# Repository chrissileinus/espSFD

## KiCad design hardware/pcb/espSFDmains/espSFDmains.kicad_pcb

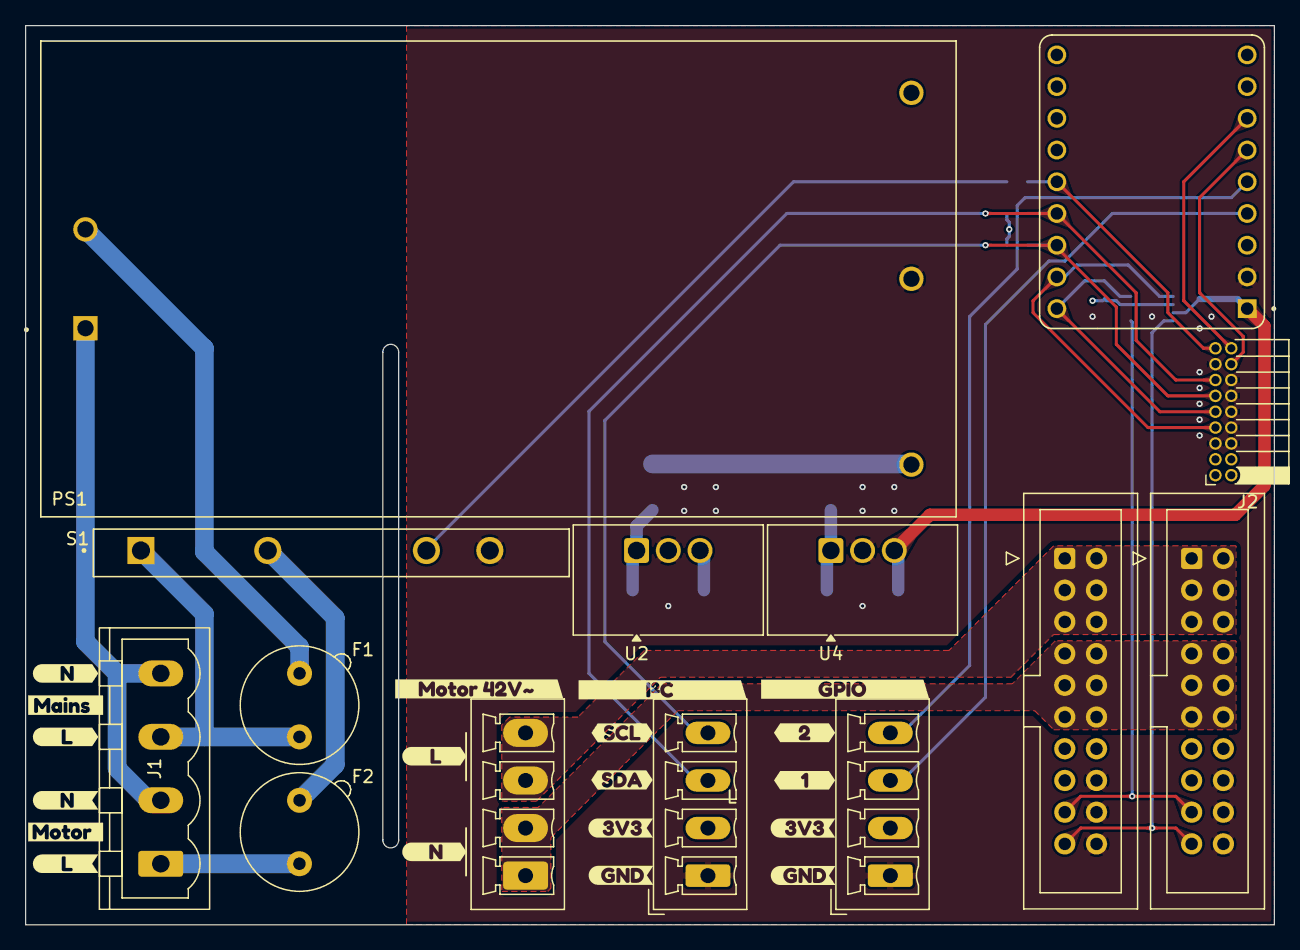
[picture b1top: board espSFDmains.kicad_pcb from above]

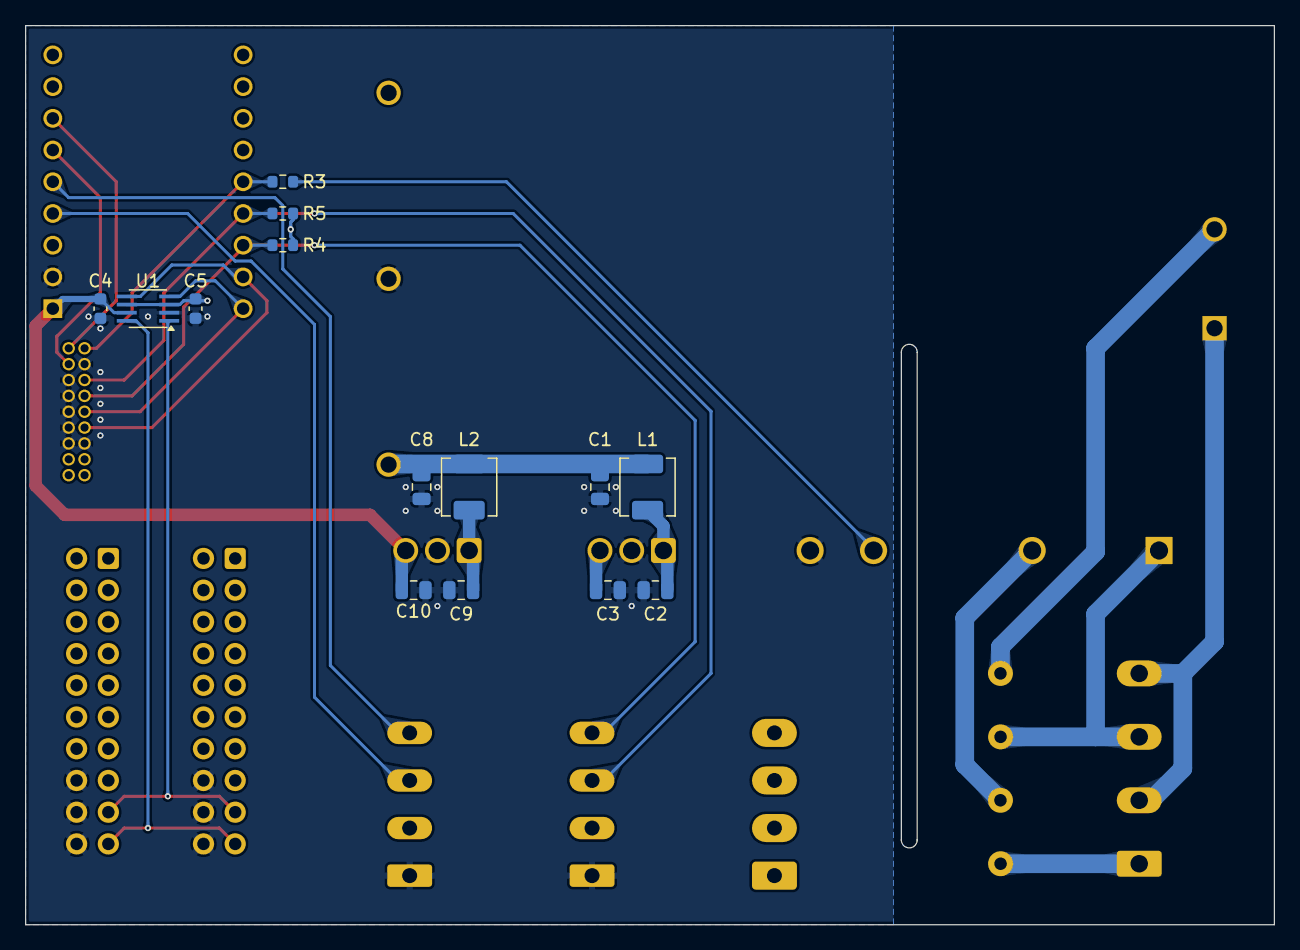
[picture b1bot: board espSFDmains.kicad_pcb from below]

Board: 4 copper layers, 100.0 x 72.0 mm, 47 parts (14 on the bottom side), 25 nets.

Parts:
C1, C2, C8, C9: 4.7µF 50V; C_0805_2012Metric
C3, C10: 10µF 25V; C_0805_2012Metric
C4, C5: 100nF/25V; C_0603_1608Metric
F1: 1A; Fuseholder_TR5_Littelfuse_No560_No460
F2: 6A; Fuseholder_TR5_Littelfuse_No560_No460
J1: Mains; PhoenixContact_MSTBVA_2,5_4-G-5,08_1x04_P5.08mm_Vertical
J2: Board Interconn; PinSocket_2x09_P1.27mm_Horizontal
J5: Motor; PhoenixContact_MCV_1,5_4-G-3.81_1x04_P3.81mm_Vertical
J8, J9: SFD Bus; IDC-Header_2x10_P2.54mm_Vertical
J10: D1 & D2; PhoenixContact_MCV_1,5_4-G-3.81_1x04_P3.81mm_Vertical
J11: D3 & D4; PhoenixContact_MCV_1,5_4-G-3.81_1x04_P3.81mm_Vertical
L1, L2: 4,7µH 3A; L_Sunlord_MWSA0402S
PS1: TPP_30-109-D
R3: 330R; R_0603_1608Metric
R4, R5: 4K7; R_0603_1608Metric
S1: CPC40055ST
U1: TXS0102DCT; SSOP-8_2.95x2.8mm_P0.65mm
U2: TSR3-2433N; Converter_DCDC_TRACO_TSR2-24xxN_TSR2-24xxxN_THT
U3: ESP32-S3-ZERO
U4: TSR3-2450N; Converter_DCDC_TRACO_TSR2-24xxN_TSR2-24xxxN_THT
kibuzzard-69B3E2B0: G***; kibuzzard-69B3E2B0
kibuzzard-69B3E2CA: G***; kibuzzard-69B3E2CA
kibuzzard-69B3E35C: G***; kibuzzard-69B3E35C
kibuzzard-69B3E36A: G***; kibuzzard-69B3E36A
kibuzzard-69B3E36E: G***; kibuzzard-69B3E36E
kibuzzard-69B3E37F: G***; kibuzzard-69B3E37F
kibuzzard-69B3E350: G***; kibuzzard-69B3E350
kibuzzard-69B3E357: G***; kibuzzard-69B3E357
kibuzzard-69B3E365: G***; kibuzzard-69B3E365
kibuzzard-69B3E379: G***; kibuzzard-69B3E379
kibuzzard-69B3E384: G***; kibuzzard-69B3E384
kibuzzard-69B3E389: G***; kibuzzard-69B3E389
kibuzzard-699C2DF3: G***; kibuzzard-699C2DF3
kibuzzard-699C2E08: G***; kibuzzard-699C2E08
kibuzzard-699C2E52: G***; kibuzzard-699C2E52
kibuzzard-699C2EF8: G***; kibuzzard-699C2EF8
kibuzzard-699C2F02: G***; kibuzzard-699C2F02
kibuzzard-6985EF5B: G***; kibuzzard-6985EF5B
kibuzzard-6985EF62: G***; kibuzzard-6985EF62

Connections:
230V Motor: F2.1, J1.1
+3.3V: C3.2, C5.2, J10.2, J11.2, R4.1, R5.1, U1.3 (VCCA), U1.6 (OE), U2.3 (Vout)
+5V: C4.2, C10.2, U1.7 (VCCB), U3.5V, U4.3 (Vout)
+9V: C1.2, C8.2, J2.1, J2.2, J2.3, J2.4, J8.13, J8.14, J8.15, J9.13, J9.14, J9.15, L1.1, L2.1, PS1.3 (+VOUT)
En Motor: J2.17, R3.1, U3.11 (GP11)
GND: C1.1, C2.1, C3.1, C4.1, C5.1, C8.1, C9.1, C10.1, J2.5, J2.6, J2.8, J2.10, J2.12, J2.14, J2.15, J8.16, J8.18, J8.20, J9.16, J9.18, J9.20, J10.1, J11.1, PS1.4 (-VOUT), S1.4 (-LED), U1.2 (GND), U2.2 (GND), U3.GND, U4.2 (GND)
GPIO1: J11.3, U3.1 (GP1)
GPIO2: J11.4, U3.2 (GP2)
GPIO3: J2.16, U3.3 (GP3)
GPIO4: J2.18, U3.4 (GP4)
LINE: F1.1, J1.3, S1.1 (AC_LOAD1)
Motor L: J5.1, J5.2, J8.7, J8.8, J8.9, J8.10, J8.11, J8.12, J9.7, J9.8, J9.9, J9.10, J9.11, J9.12
Motor N: J5.3, J5.4, J8.1, J8.2, J8.3, J8.4, J8.5, J8.6, J9.1, J9.2, J9.3, J9.4, J9.5, J9.6
NEUT: J1.2, J1.4, PS1.1 (NEUTRAL)
unnamed: F1.2, PS1.2 (LINE)
unnamed: R3.2, S1.3 (+LED)
unnamed: F2.2, S1.2 (AC_LOAD2)
unnamed: C2.2, L1.2, U2.1 (Vin)
unnamed: C9.2, L2.2, U4.1 (Vin)
RX: J8.19, J9.19, U1.8 (B1)
RX_: J2.7, U1.5 (A1), U3.RX
SCL: J2.11, J10.4, R4.2, U3.13 (GP13)
SDA: J2.13, J10.3, R5.2, U3.12 (GP12)
TX: J8.17, J9.17, U1.1 (B2)
TX_: J2.9, U1.4 (A2), U3.TX

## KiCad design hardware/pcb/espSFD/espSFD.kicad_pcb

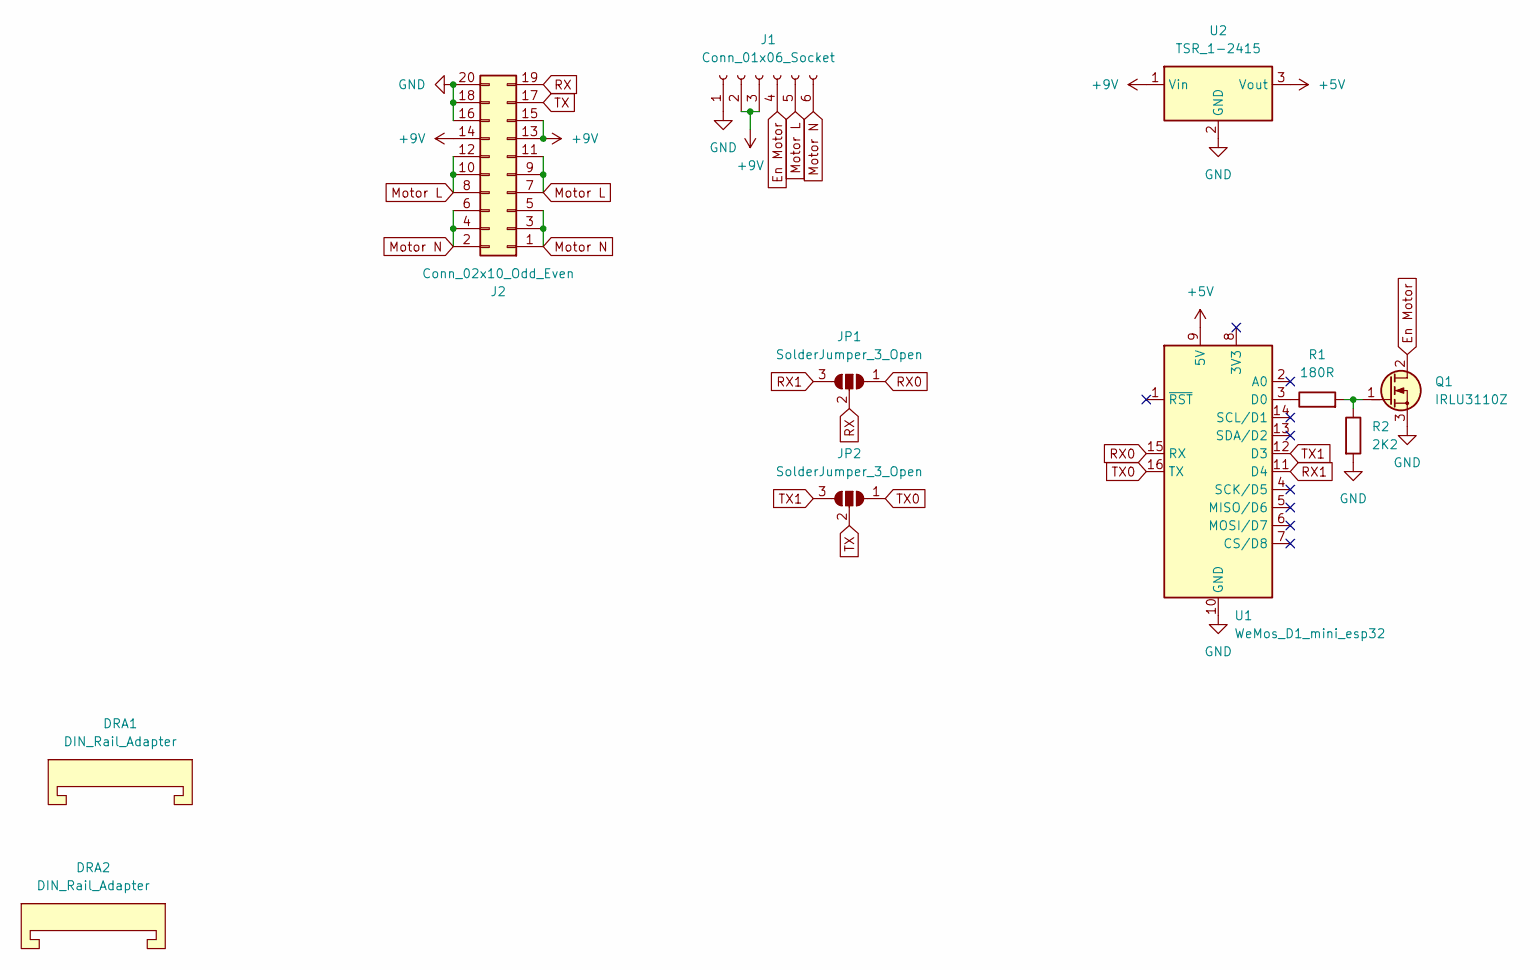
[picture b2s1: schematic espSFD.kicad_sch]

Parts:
DRA1, DRA2: DIN_Rail_Adapter; DINRailAdapter_3xM3_PhoenixContact_1201578
J1: Conn_01x06_Socket; PhoenixContact_MSTBA_2,5_6-G-5,08_1x06_P5.08mm_Horizontal
J2: Conn_02x10_Odd_Even; IDC-Header_2x10_P2.54mm_Vertical
JP1, JP2: SolderJumper_3_Open; SolderJumper-3_P1.3mm_Open_Pad1.0x1.5mm no silk
Q1: IRLU3110Z; TO-251-3_Vertical_GDS
R1: 180R; R_Axial_DIN0204_L3.6mm_D1.6mm_P7.62mm_Horizontal
R2: 2K2; R_Axial_DIN0204_L3.6mm_D1.6mm_P7.62mm_Horizontal
U1: WeMos_D1_mini_esp32; WEMOS_D1_mini_light
U2: TSR_1-2415; Converter_DCDC_TRACO_TSR-1_THT

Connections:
+5V: U1.9 (5V), U2.3 (Vout)
+9V: J1.2, J1.3, J2.13, J2.14, J2.15, U2.1 (Vin)
En Motor: J1.4, Q1.2 (D)
GND: J1.1, J2.16, J2.18, J2.20, Q1.3 (S), R2.2, U1.10 (GND), U2.2 (GND)
Motor L: J1.5, J2.7, J2.8, J2.9, J2.10, J2.11, J2.12
Motor N: J1.6, J2.1, J2.2, J2.3, J2.4, J2.5, J2.6
unnamed: Q1.1 (G), R1.2, R2.1
unnamed: R1.1, U1.3 (D0)
RX: J2.19, JP1.2 (C)
RX0: JP1.1 (A), U1.15 (RX)
RX1: JP1.3 (B), U1.11 (D4)
TX: J2.17, JP2.2 (C)
TX0: JP2.1 (A), U1.16 (TX)
TX1: JP2.3 (B), U1.12 (D3)

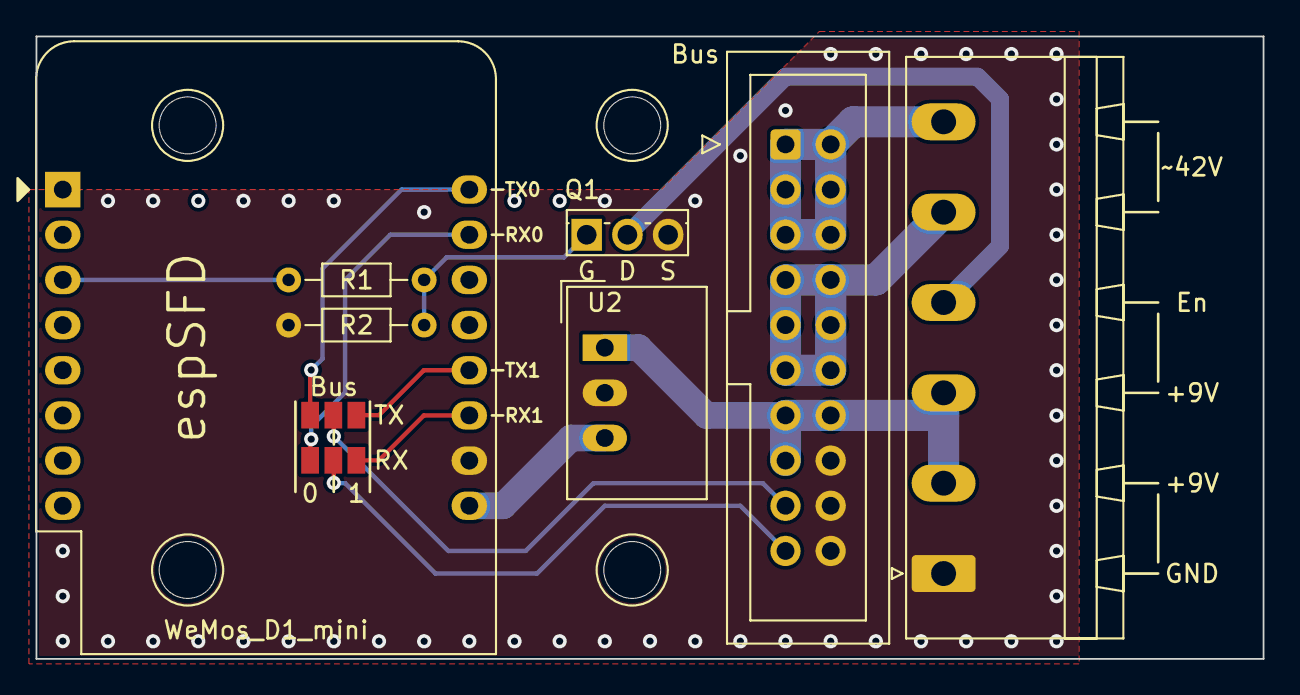
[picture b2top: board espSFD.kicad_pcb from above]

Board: 2 copper layers, 69.0 x 35.0 mm, 11 parts (0 on the bottom side), 14 nets.

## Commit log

2024-01-17 First Init
2024-01-17 gsdfhg
2024-01-17 sfhds
2024-01-18 es dghdgfj fcgj
2024-01-19 dfhd
2024-01-19 fhdsgf
2024-01-19 fh dyfh
2024-01-19 fdhd
2024-01-24 hdfh
2024-01-24 add espSFDmains
2024-01-26 ghjfgj
2024-03-15 fdshd f
2024-03-22 etw erzt
2024-03-27 gfjhdfjh
2024-03-28 bsfnbdfnb
2024-04-02 hfdghd
2024-04-02 fdhb
2025-03-21 fbxcv
2025-03-21 rsgs
2025-03-21 dgsd
2025-03-21 fdsh
2025-04-10 rhdfh
2025-04-10 fhdhf
2025-04-16 turu
2026-01-29 PCB V1.2
2026-01-29 ghfd
2026-01-30 jfgj
2026-02-02 frhgfd
2026-02-03 fhdgfh
2026-02-04 hedfhf
2026-02-09 vncvn
2026-02-17 ffd hdf
2026-02-20 fd hfh
2026-02-20 bg df
2026-02-21 fhgfds hds
2026-02-23 ffg dsfb
2026-03-13 bxcbxc
2026-04-13 teruzrtu
